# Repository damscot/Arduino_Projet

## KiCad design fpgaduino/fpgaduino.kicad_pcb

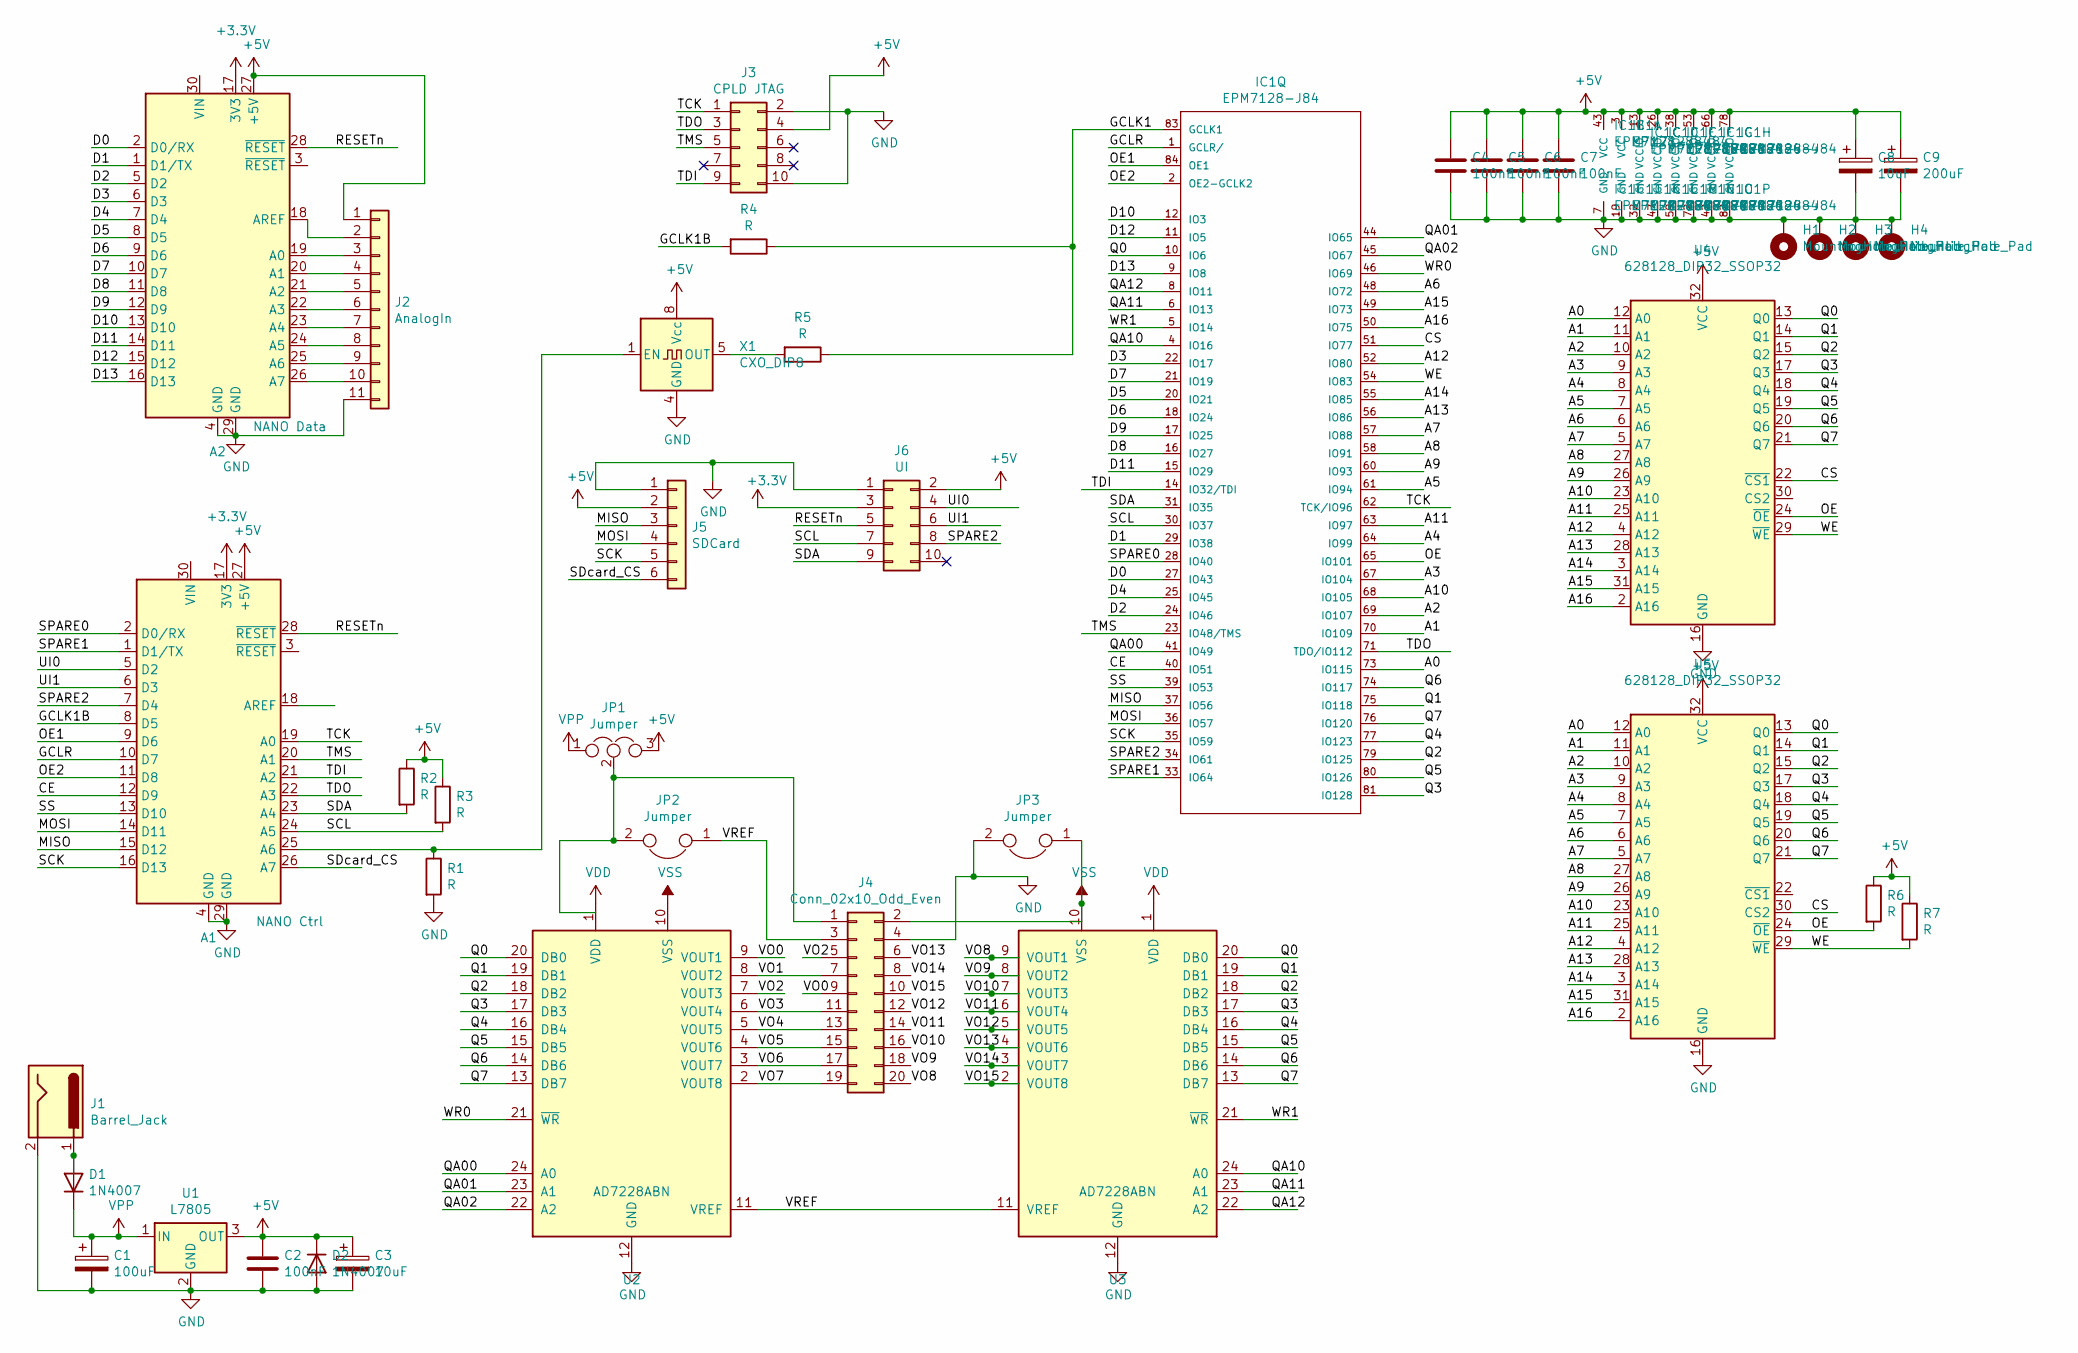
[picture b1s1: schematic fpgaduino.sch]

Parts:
A1: NANO Ctrl; Arduino_Nano
A2: NANO Data; Arduino_Nano
C1: 100uF; C_Radial_D6.3mm_H11.0mm_P2.50mm
C2, C4, C5, C6, C7: 100nF; C_Rect_L7.0mm_W2.0mm_P5.00mm
C3, C8: 10uF; C_Radial_D6.3mm_H11.0mm_P2.50mm
C9: 200uF; C_Radial_D6.3mm_H11.0mm_P2.50mm
D1, D2: 1N4007; D_DO-41_SOD81_P10.16mm_Horizontal
H1, H2, H3, H4: MountingHole_Pad; MountingHole_3.2mm_M3_ISO14580_Pad
IC1: EPM7128-J84; PLCC-84_THT-Socket
J1: Barrel_Jack; BarrelJack_Horizontal
J2: AnalogIn; PinHeader_1x11_P2.54mm_Vertical
J3: CPLD JTAG; IDC-Header_2x05_P2.54mm_Vertical
J4: Conn_02x10_Odd_Even; PinHeader_2x10_P2.54mm_Vertical
J5: SDCard; PinHeader_1x06_P2.54mm_Vertical
J6: UI; IDC-Header_2x05_P2.54mm_Vertical
JP1: Jumper; PinHeader_1x03_P2.54mm_Vertical
JP2, JP3: Jumper; PinHeader_1x02_P2.54mm_Vertical
R1, R2, R3, R4, R5, R6, R7: R; R_Axial_DIN0207_L6.3mm_D2.5mm_P10.16mm_Horizontal
U1: L7805; TO-220-3_Vertical
U2, U3: AD7228ABN; DIP-24_W7.62mm_Socket_LongPads
U4, U5: 628128_DIP32_SSOP32; DIP-32_W15.24mm_Socket_LongPads
X1: CXO_DIP8; Oscillator_DIP-8_LargePads

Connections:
+3V3: A1.17 (3V3), A2.17 (3V3), J6.3
+5V: A1.27 (+5V), A2.27 (+5V), C2.1, C3.1, C4.1, C5.1, C6.1, C7.1, C8.1, C9.1, D2.1 (K), IC1.3 (VCC), IC1.13 (VCCIO), IC1.26 (VCCIO), IC1.38 (VCCIO), IC1.43 (VCC), IC1.53 (VCCIO), IC1.66 (VCCIO), IC1.78 (VCCIO), J2.1, J3.4, J5.2, J6.2, JP1.3, R2.1, R3.1, R6.1, R7.1, U1.3 (OUT), U4.32 (VCC), U5.32 (VCC), X1.8 (Vcc)
/A0: IC1.73 (IO115), U4.12 (A0), U5.12 (A0)
/A1: IC1.70 (IO109), U4.11 (A1), U5.11 (A1)
/A2: IC1.69 (IO107), U4.10 (A2), U5.10 (A2)
/A3: IC1.67 (IO104), U4.9 (A3), U5.9 (A3)
/A4: IC1.64 (IO99), U4.8 (A4), U5.8 (A4)
/A5: IC1.61 (IO94), U4.7 (A5), U5.7 (A5)
/A6: IC1.48 (IO72), U4.6 (A6), U5.6 (A6)
/A7: IC1.57 (IO88), U4.5 (A7), U5.5 (A7)
/A8: IC1.58 (IO91), U4.27 (A8), U5.27 (A8)
/A9: IC1.60 (IO93), U4.26 (A9), U5.26 (A9)
/A10: IC1.68 (IO105), U4.23 (A10), U5.23 (A10)
/A11: IC1.63 (IO97), U4.25 (A11), U5.25 (A11)
/A12: IC1.52 (IO80), U4.4 (A12), U5.4 (A12)
/A13: IC1.56 (IO86), U4.28 (A13), U5.28 (A13)
/A14: IC1.55 (IO85), U4.3 (A14), U5.3 (A14)
/A15: IC1.49 (IO73), U4.31 (A15), U5.31 (A15)
/A16: IC1.50 (IO75), U4.2 (A16), U5.2 (A16)
/CE: A1.12 (D9), IC1.40 (IO51)
/CS: IC1.51 (IO77), U4.22 (~CS1), U5.30 (CS2)
/D0: A2.2 (D0/RX), IC1.27 (IO43)
/D1: A2.1 (D1/TX), IC1.29 (IO38)
/D2: A2.5 (D2), IC1.24 (IO46)
/D3: A2.6 (D3), IC1.22 (IO17)
/D4: A2.7 (D4), IC1.25 (IO45)
/D5: A2.8 (D5), IC1.20 (IO21)
/D6: A2.9 (D6), IC1.18 (IO24)
/D7: A2.10 (D7), IC1.21 (IO19)
/D8: A2.11 (D8), IC1.16 (IO27)
/D9: A2.12 (D9), IC1.17 (IO25)
/D10: A2.13 (D10), IC1.12 (IO3)
/D11: A2.14 (D11), IC1.15 (IO29)
/D12: A2.15 (D12), IC1.11 (IO5)
/D13: A2.16 (D13), IC1.9 (IO8)
/GCLK1: IC1.83 (GCLK1), R4.1, R5.1
/GCLK1B: A1.8 (D5), R4.2
/GCLR: A1.10 (D7), IC1.1 (GCLR/)
/MISO: A1.15 (D12), IC1.37 (IO56), J5.3
/MOSI: A1.14 (D11), IC1.36 (IO57), J5.4
/OE: IC1.65 (IO101), R6.2, U4.24 (~OE), U5.24 (~OE)
/OE1: A1.9 (D6), IC1.84 (OE1)
/OE2: A1.11 (D8), IC1.2 (OE2-GCLK2)
/Q0: IC1.10 (IO6), U2.20 (DB0), U3.20 (DB0), U4.13 (Q0), U5.13 (Q0)
/Q1: IC1.75 (IO118), U2.19 (DB1), U3.19 (DB1), U4.14 (Q1), U5.14 (Q1)
/Q2: IC1.79 (IO125), U2.18 (DB2), U3.18 (DB2), U4.15 (Q2), U5.15 (Q2)
/Q3: IC1.81 (IO128), U2.17 (DB3), U3.17 (DB3), U4.17 (Q3), U5.17 (Q3)
/Q4: IC1.77 (IO123), U2.16 (DB4), U3.16 (DB4), U4.18 (Q4), U5.18 (Q4)
/Q5: IC1.80 (IO126), U2.15 (DB5), U3.15 (DB5), U4.19 (Q5), U5.19 (Q5)
/Q6: IC1.74 (IO117), U2.14 (DB6), U3.14 (DB6), U4.20 (Q6), U5.20 (Q6)
/Q7: IC1.76 (IO120), U2.13 (DB7), U3.13 (DB7), U4.21 (Q7), U5.21 (Q7)
/QA00: IC1.41 (IO49), U2.24 (A0)
/QA01: IC1.44 (IO65), U2.23 (A1)
/QA02: IC1.45 (IO67), U2.22 (A2)
/QA10: IC1.4 (IO16), U3.24 (A0)
/QA11: IC1.6 (IO13), U3.23 (A1)
/QA12: IC1.8 (IO11), U3.22 (A2)
/RESETn: A1.28 (~RESET), A2.28 (~RESET), J6.5
/SCK: A1.16 (D13), IC1.35 (IO59), J5.5
/SCL: A1.24 (A5), IC1.30 (IO37), J6.7, R3.2
/SDA: A1.23 (A4), IC1.31 (IO35), J6.9, R2.2
/SDcard_CS: A1.26 (A7), J5.6
/SPARE0: A1.2 (D0/RX), IC1.28 (IO40)
/SPARE1: A1.1 (D1/TX), IC1.33 (IO64)
/SPARE2: A1.7 (D4), IC1.34 (IO61), J6.8
/SS: A1.13 (D10), IC1.39 (IO53)
/TCK: A1.19 (A0), IC1.62 (TCK/IO96), J3.1
/TDI: A1.21 (A2), IC1.14 (IO32/TDI), J3.9
/TDO: A1.22 (A3), IC1.71 (TDO/IO112), J3.3
/TMS: A1.20 (A1), IC1.23 (IO48/TMS), J3.5
/UI0: A1.5 (D2), J6.4
/UI1: A1.6 (D3), J6.6
/VO0: J4.9, U2.9 (VOUT1)
/VO1: J4.7, U2.8 (VOUT2)
/VO2: J4.5, U2.7 (VOUT3)
/VO3: J4.11, U2.6 (VOUT4)
/VO4: J4.13, U2.5 (VOUT5)
/VO5: J4.15, U2.4 (VOUT6)
/VO6: J4.17, U2.3 (VOUT7)
/VO7: J4.19, U2.2 (VOUT8)
/VO8: J4.20, U3.9 (VOUT1)
/VO9: J4.18, U3.8 (VOUT2)
/VO10: J4.16, U3.7 (VOUT3)
/VO11: J4.14, U3.6 (VOUT4)
/VO12: J4.12, U3.5 (VOUT5)
/VO13: J4.6, U3.4 (VOUT6)
/VO14: J4.8, U3.3 (VOUT7)
/VO15: J4.10, U3.2 (VOUT8)
/VREF: J4.3, JP2.1, U2.11 (VREF), U3.11 (VREF)
/WE: IC1.54 (IO83), R7.2, U4.29 (~WE), U5.29 (~WE)
/WR0: IC1.46 (IO69), U2.21 (~WR)
/WR1: IC1.5 (IO14), U3.21 (~WR)
GND: A1.4 (GND), A1.29 (GND), A2.4 (GND), A2.29 (GND), C1.2, C2.2, C3.2, C4.2, C5.2, C6.2, C7.2, C8.2, C9.2, D2.2 (A), H1.1, H2.1, H3.1, H4.1, IC1.7 (GND), IC1.19 (GND), IC1.32 (GND), IC1.42 (GND), IC1.47 (GND), IC1.59 (GND), IC1.72 (GND), IC1.82 (GND), J1.2, J2.11, J3.2, J3.10, J4.4, J5.1, J6.1, JP3.2, R1.2, U1.2 (GND), U2.12 (GND), U3.12 (GND), U4.16 (GND), U5.16 (GND), X1.4 (GND)
unnamed: A1.25 (A6), R1.1, X1.1 (EN)
unnamed: A2.18 (AREF), J2.2
unnamed: A2.19 (A0), J2.3
unnamed: A2.20 (A1), J2.4
unnamed: A2.21 (A2), J2.5
unnamed: A2.22 (A3), J2.6
unnamed: A2.23 (A4), J2.7
unnamed: A2.24 (A5), J2.8
unnamed: A2.25 (A6), J2.9
unnamed: A2.26 (A7), J2.10
unnamed: D1.2 (A), J1.1
unnamed: J4.1, JP1.2, JP2.2
unnamed: R5.2, X1.5 (OUT)
VDD: U2.1 (VDD), U3.1 (VDD)
VPP: C1.1, D1.1 (K), JP1.1, U1.1 (IN)
VSS: J4.2, JP3.1, U2.10 (VSS), U3.10 (VSS)

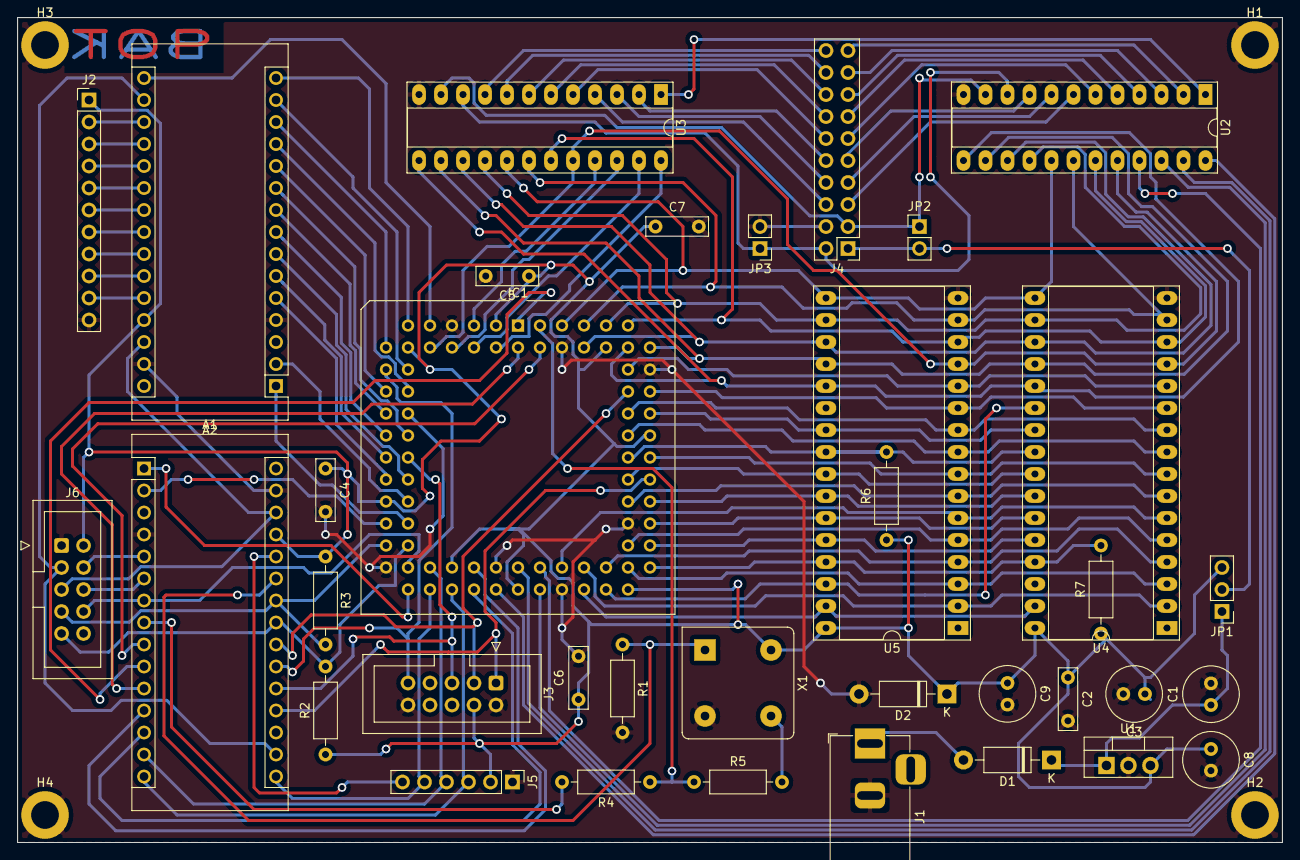
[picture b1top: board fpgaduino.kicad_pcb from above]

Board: 2 copper layers, 146.1 x 95.2 mm, 40 parts (0 on the bottom side), 109 nets.

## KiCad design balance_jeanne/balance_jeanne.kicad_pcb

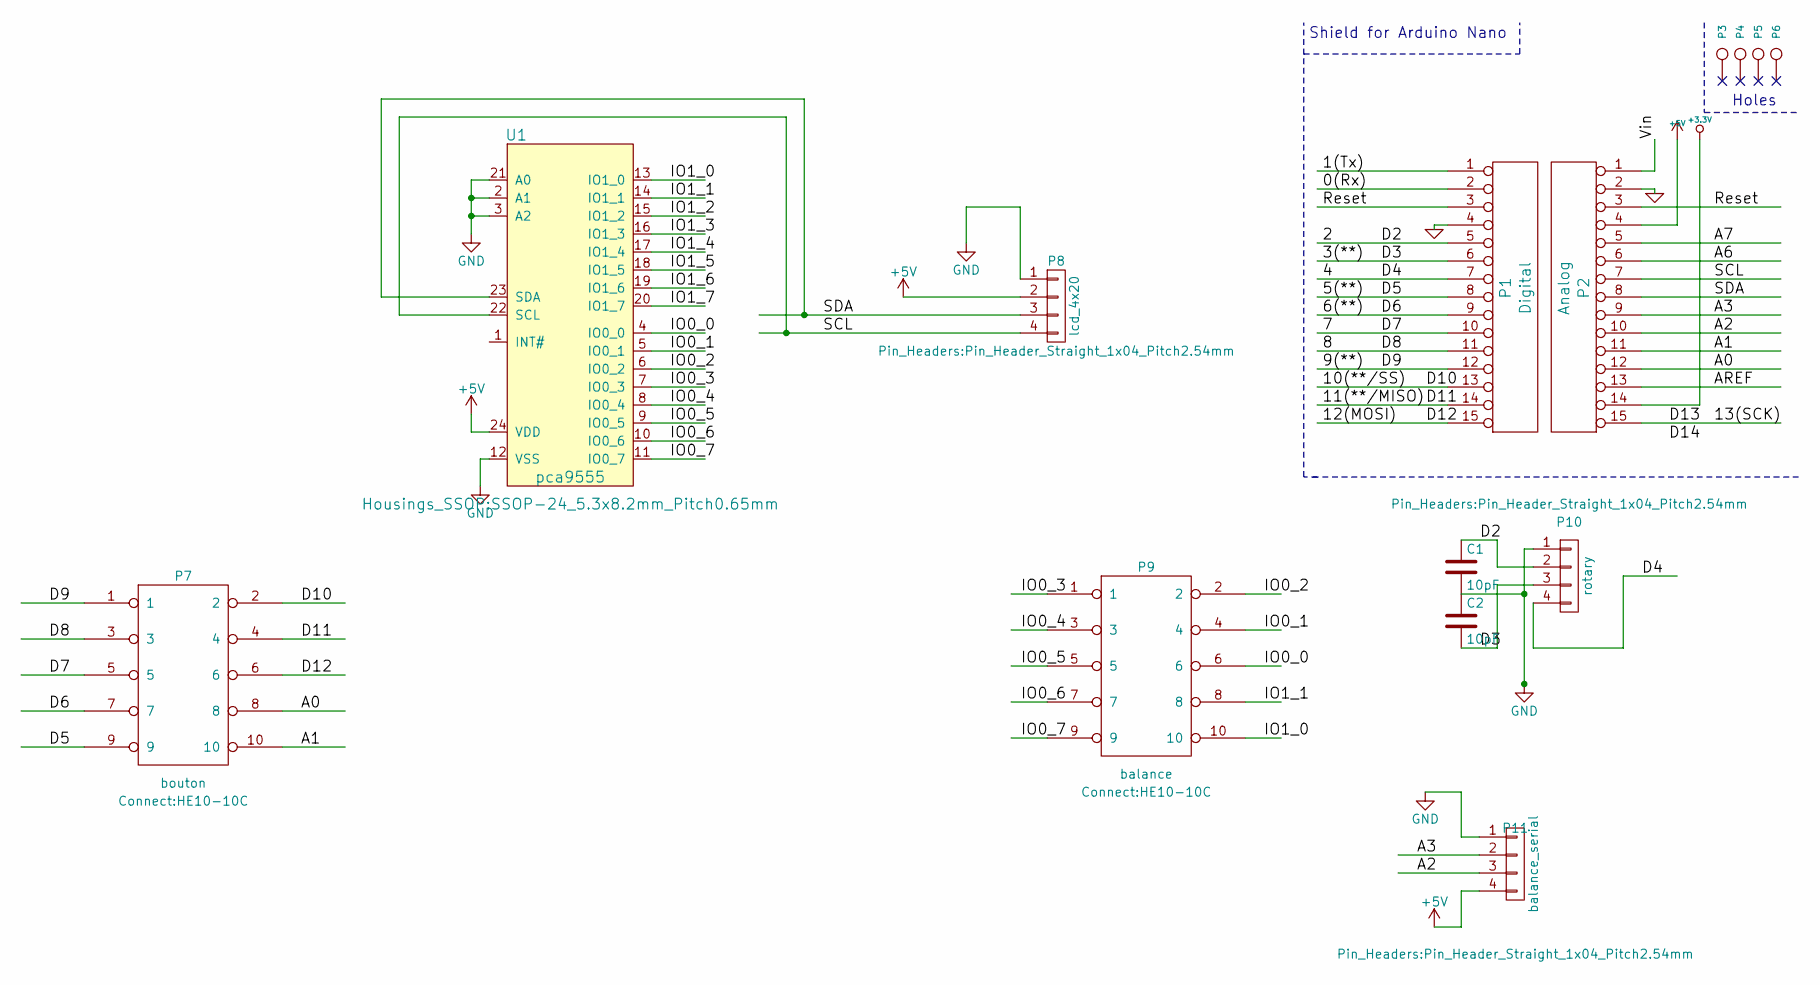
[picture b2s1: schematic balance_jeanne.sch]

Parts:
C1, C2: 10pF; Pin_Header_Straight_1x02_Pitch2.54mm
P1: Digital; Socket_Strip_Arduino_1x15
P2: Analog; Socket_Strip_Arduino_1x15
P3, P4, P5, P6: CONN_1; 1pin_Nano
P7: bouton; HE10-10C
P8: lcd_4x20; Pin_Header_Straight_1x04_Pitch2.54mm
P9: balance; HE10-10C
P10: rotary; Pin_Header_Straight_1x04_Pitch2.54mm
P11: balance_serial; Pin_Header_Straight_1x04_Pitch2.54mm
U1: pca9555; SSOP-24_5.3x8.2mm_Pitch0.65mm

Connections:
+3.3V: P2.14
+5V: P2.4, P8.2, P11.4, U1.24 (VDD)
/0(Rx): P1.2
/1(Tx): P1.1
/2: C1.1, P1.5, P10.2
/3(**): C2.2, P1.6, P10.3
/4: P1.7, P10.4
/5(**): P1.8, P7.9
/6(**): P1.9, P7.7
/7: P1.10, P7.5
/8: P1.11, P7.3
/9(**): P1.12, P7.1
/10(**/SS): P1.13, P7.2
/11(**/MISO): P1.14, P7.4
/12(MOSI): P1.15 (p15), P7.6
/13(SCK): P2.15 (p15)
/A0: P2.12, P7.8
/A1: P2.11, P7.10
/A2: P2.10, P11.3
/A3: P2.9, P11.2
/A6: P2.6
/A7: P2.5
/AREF: P2.13
/IO0_0: P9.6, U1.4 (IO0_0)
/IO0_1: P9.4, U1.5 (IO0_1)
/IO0_2: P9.2, U1.6 (IO0_2)
/IO0_3: P9.1, U1.7 (IO0_3)
/IO0_4: P9.3, U1.8 (IO0_4)
/IO0_5: P9.5, U1.9 (IO0_5)
/IO0_6: P9.7, U1.10 (IO0_6)
/IO0_7: P9.9, U1.11 (IO0_7)
/IO1_0: P9.10, U1.13 (IO1_0)
/IO1_1: P9.8, U1.14 (IO1_1)
/IO1_2: U1.15 (IO1_2)
/IO1_3: U1.16 (IO1_3)
/IO1_4: U1.17 (IO1_4)
/IO1_5: U1.18 (IO1_5)
/IO1_6: U1.19 (IO1_6)
/IO1_7: U1.20 (IO1_7)
/Reset: P1.3, P2.3
/SCL: P2.7, P8.4, U1.22 (SCL)
/SDA: P2.8, P8.3, U1.23 (SDA)
/Vin: P2.1
GND: C1.2, C2.1, P1.4, P2.2, P8.1, P10.1, P11.1, U1.2 (A1), U1.3 (A2), U1.12 (VSS), U1.21 (A0)

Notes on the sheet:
Holes
Shield for Arduino Nano

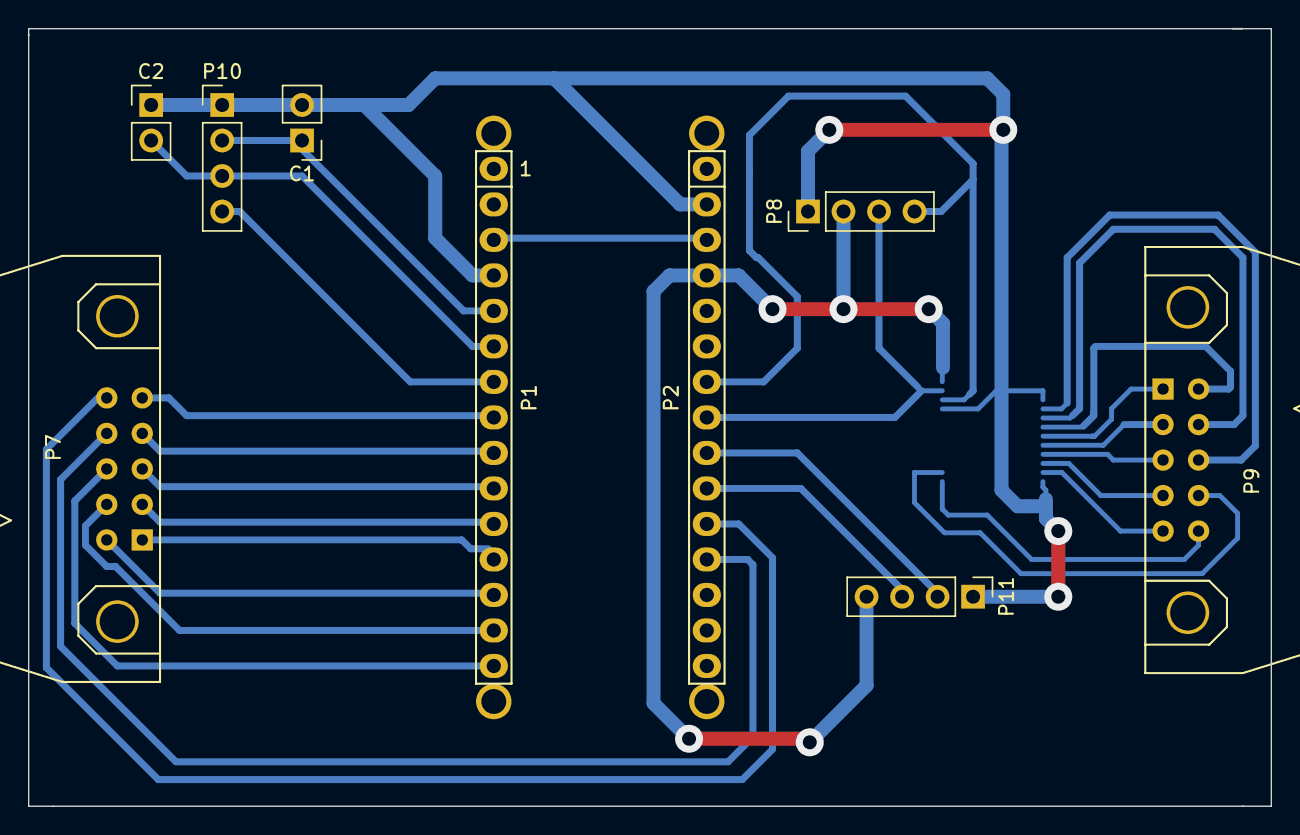
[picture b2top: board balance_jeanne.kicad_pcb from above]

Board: 2 copper layers, 88.9 x 55.6 mm, 14 parts (1 on the bottom side), 30 nets.

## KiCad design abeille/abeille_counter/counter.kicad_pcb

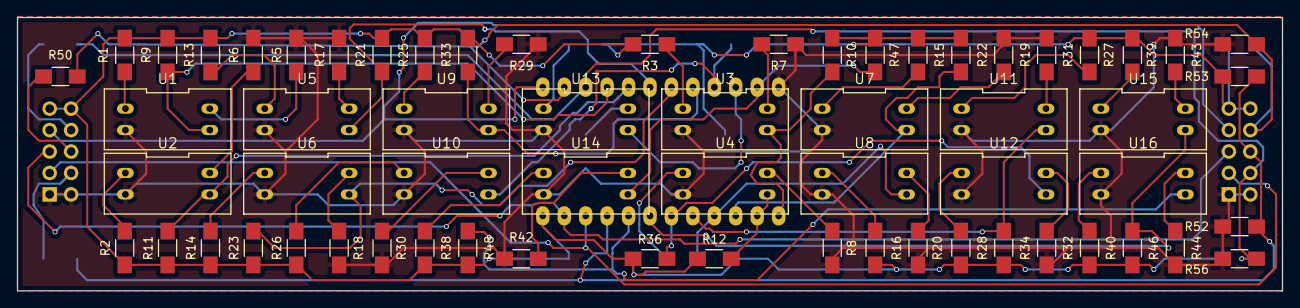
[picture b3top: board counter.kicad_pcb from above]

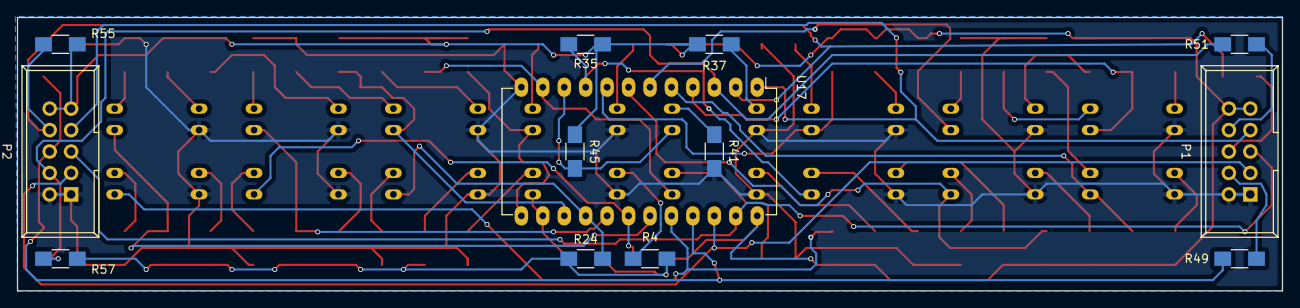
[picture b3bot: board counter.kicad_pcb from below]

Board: 2 copper layers, 149.9 x 32.4 mm, 76 parts (13 on the bottom side), 59 nets.

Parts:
P1, P2: HE10-10; IDC_Header_Straight_10pins
R1, R2, R3, R4, R5, R6, R7, R8, R13, R14, R15, R16, R17, R18, R19, R20, R25, R26, R27, R28, R29, R30, R31, R32, R37, R38, R39, R40, R41, R42, R43, R44: 1K; R_1206_HandSoldering
R9, R10, R11, R12, R21, R22, R23, R24, R33, R34, R35, R36, R45, R46, R47, R48: 100K; R_1206_HandSoldering
R49, R50, R51, R52, R53, R54, R55, R56, R57: 0; R_1206_HandSoldering
U1: IN_0; ITR9608_DIP-4_0_ELL
U2: OUT_0; ITR9608_DIP-4_0_ELL
U3: IN_4; ITR9608_DIP-4_0_ELL
U4: OUT_4; ITR9608_DIP-4_0_ELL
U5: IN_1; ITR9608_DIP-4_0_ELL
U6: OUT_1; ITR9608_DIP-4_0_ELL
U7: IN_5; ITR9608_DIP-4_0_ELL
U8: OUT_5; ITR9608_DIP-4_0_ELL
U9: IN_2; ITR9608_DIP-4_0_ELL
U10: OUT_2; ITR9608_DIP-4_0_ELL
U11: IN_6; ITR9608_DIP-4_0_ELL
U12: OUT_6; ITR9608_DIP-4_0_ELL
U13: IN_3; ITR9608_DIP-4_0_ELL
U14: OUT_3; ITR9608_DIP-4_0_ELL
U15: IN_7; ITR9608_DIP-4_0_ELL
U16: OUT_7; ITR9608_DIP-4_0_ELL
U17: pca9555; DIP-24_W15.24mm_LongPads

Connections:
+5V: P1.9, P1.10, P2.9, P2.10, R1.1, R2.1, R3.1, R4.1, R9.1, R10.1, R11.1, R12.1, R13.1, R14.1, R15.1, R16.1, R21.1, R22.1, R23.1, R24.1, R25.1, R26.1, R27.1, R28.1, R33.1, R34.1, R35.1, R36.1, R37.1, R38.1, R39.1, R40.1, R45.1, R46.1, R47.1, R48.1, R53.2, R55.2, R57.2, U17.24
/A0: P2.6, R49.1, R52.2, R53.1, U17.21
/A1: P2.8, R50.1, R54.2, R55.1, U17.2
/A2: P2.4, R51.1, R56.2, R57.1, U17.3
/D0: R9.2, U1.3, U17.4
/D1: R11.2, U2.3, U17.5
/D2: R21.2, U5.3, U17.6
/D3: R23.2, U6.3, U17.7
/D4: R33.2, U9.3, U17.8
/D5: R35.2, U10.3, U17.9
/D6: R45.2, U13.3, U17.10
/D7: R47.2, U14.3, U17.11
/D8: R10.2, U3.3, U17.13
/D9: R12.2, U4.3, U17.14
/D10: R22.2, U7.3, U17.15
/D11: R24.2, U8.3, U17.16
/D12: R34.2, U11.3, U17.17
/D13: R36.2, U12.3, U17.18
/D14: R46.2, U15.3, U17.19
/D15: R48.2, U16.3, U17.20
/INT#: P1.7, P2.7, U17.1
/SCL: P1.3, P2.3, U17.22
/SDA: P1.5, P2.5, U17.23
GND: P1.1, P1.2, P2.1, P2.2, R5.2, R6.2, R7.2, R8.2, R17.2, R18.2, R19.2, R20.2, R29.2, R30.2, R31.2, R32.2, R41.2, R42.2, R43.2, R44.2, R52.1, R54.1, R56.1, U1.2, U2.2, U3.2, U4.2, U5.2, U6.2, U7.2, U8.2, U9.2, U10.2, U11.2, U12.2, U13.2, U14.2, U15.2, U16.2, U17.12
unnamed: P1.4, R49.2
unnamed: P1.6, R50.2
unnamed: P1.8, R51.2
unnamed: R1.2, U1.1
unnamed: R2.2, U2.1
unnamed: R3.2, U3.1
unnamed: R4.2, U4.1
unnamed: R5.1, U1.4
unnamed: R6.1, U2.4
unnamed: R7.1, U3.4
unnamed: R8.1, U4.4
unnamed: R13.2, U5.1
unnamed: R14.2, U6.1
unnamed: R15.2, U7.1
unnamed: R16.2, U8.1
unnamed: R17.1, U5.4
unnamed: R18.1, U6.4
unnamed: R19.1, U7.4
unnamed: R20.1, U8.4
unnamed: R25.2, U9.1
unnamed: R26.2, U10.1
unnamed: R27.2, U11.1
unnamed: R28.2, U12.1
unnamed: R29.1, U9.4
unnamed: R30.1, U10.4
unnamed: R31.1, U11.4
unnamed: R32.1, U12.4
unnamed: R37.2, U13.1
unnamed: R38.2, U14.1
unnamed: R39.2, U15.1
unnamed: R40.2, U16.1
unnamed: R41.1, U13.4
unnamed: R42.1, U14.4
unnamed: R43.1, U15.4
unnamed: R44.1, U16.4

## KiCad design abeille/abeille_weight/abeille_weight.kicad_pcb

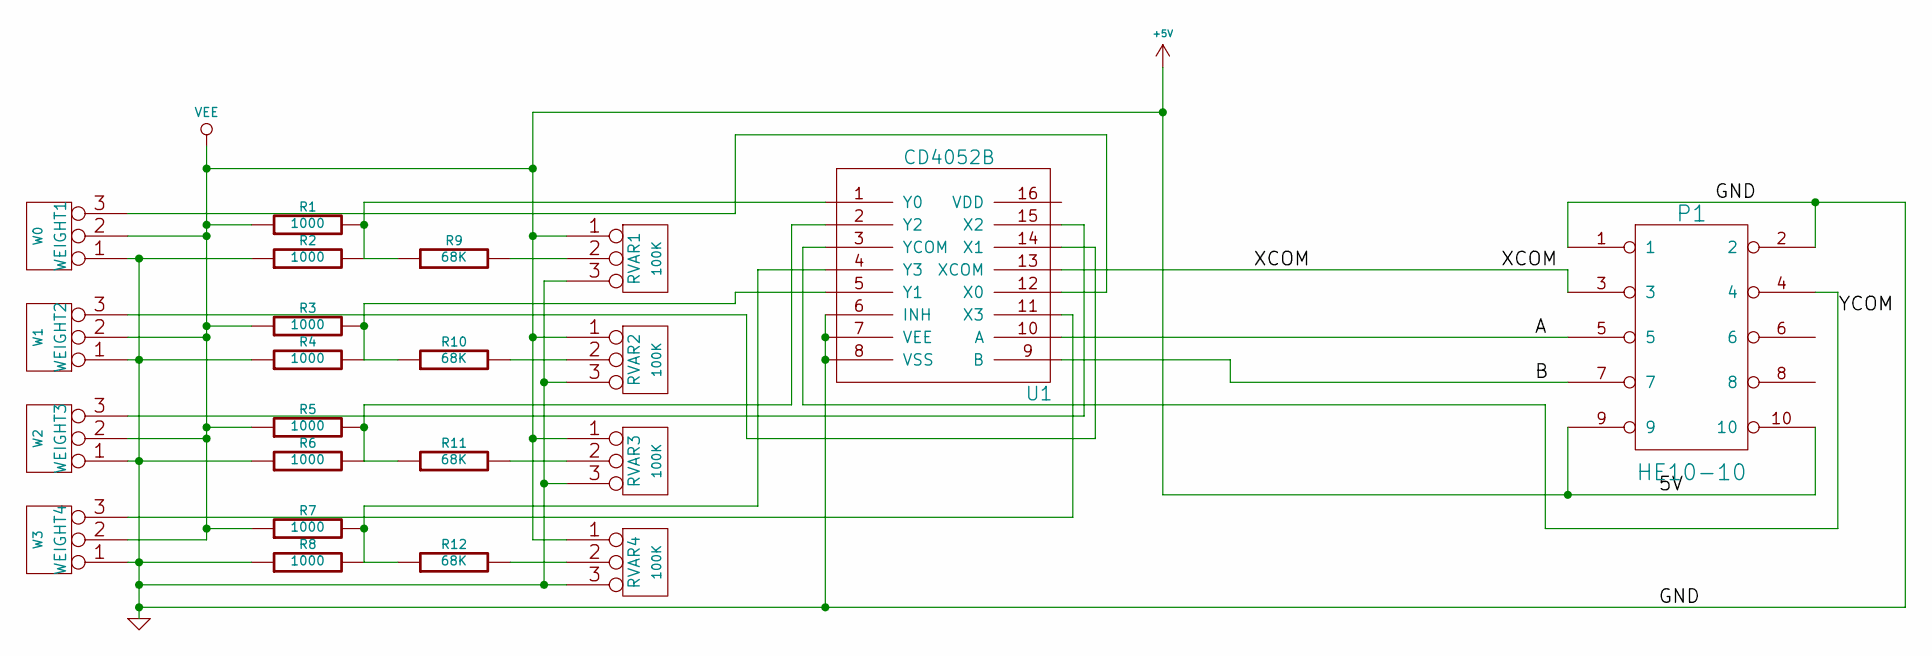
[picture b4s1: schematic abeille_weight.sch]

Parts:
P1: HE10-10
R1, R2, R3, R4, R5, R6, R7, R8: 1000
R9, R10, R11, R12: 68K
RVAR1, RVAR2, RVAR3, RVAR4: 100K
U1: CD4052B
WEIGHT1: W0
WEIGHT2: W1
WEIGHT3: W2
WEIGHT4: W3

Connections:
+5V: P1.9, P1.10, R1.1, R3.1, R5.1, R7.1, RVAR1.1, RVAR2.1, RVAR3.1, RVAR4.1, U1.16 (VDD), WEIGHT1.2 (PM), WEIGHT2.2 (PM), WEIGHT3.2 (PM), WEIGHT4.2 (PM); also elsewhere on the board
/A: P1.5, U1.10 (A)
/B: P1.7, U1.9 (B)
/DT: P1.8; also elsewhere on the board
/SCK: P1.6; also elsewhere on the board
/XCOM: P1.3, U1.13 (XCOM); also elsewhere on the board
/YCOM: P1.4, U1.3 (YCOM); also elsewhere on the board
GND: P1.1, P1.2, R2.1, R4.1, R6.1, R8.1, RVAR1.3, RVAR2.3, RVAR3.3, RVAR4.3, U1.6 (INH), U1.7 (VEE), U1.8 (VSS), WEIGHT1.1, WEIGHT2.1, WEIGHT3.1, WEIGHT4.1; also elsewhere on the board
unnamed: R1.2, R2.2, R9.1, U1.1 (Y0)
unnamed: R9.2, RVAR1.2 (PM)
unnamed: R3.2, R4.2, R10.1, U1.5 (Y1)
unnamed: R10.2, RVAR2.2 (PM)
unnamed: R5.2, R6.2, R11.1, U1.2 (Y2)
unnamed: R11.2, RVAR3.2 (PM)
unnamed: R7.2, R8.2, R12.1, U1.4 (Y3)
unnamed: R12.2, RVAR4.2 (PM)
unnamed: U1.11 (X3), WEIGHT4.3
unnamed: U1.12 (X0), WEIGHT1.3
unnamed: U1.14 (X1), WEIGHT2.3
unnamed: U1.15 (X2), WEIGHT3.3

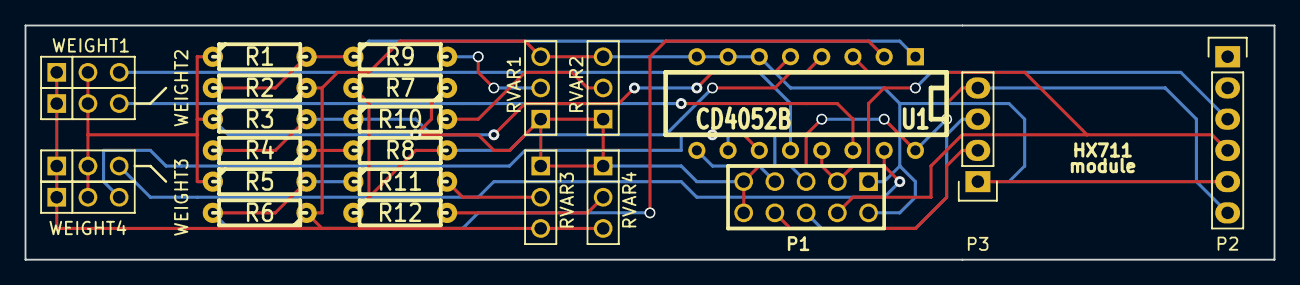
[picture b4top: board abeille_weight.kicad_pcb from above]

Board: 2 copper layers, 101.6 x 19.0 mm, 24 parts (0 on the bottom side), 20 nets.

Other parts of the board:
P2: CONN_01X06; Pin_Header_Straight_1x06
P3: CONN_01X04; Pin_Header_Straight_1x04

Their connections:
+5V: P2.6, P3.4; also elsewhere on the board
/DT: P3.2; also elsewhere on the board
/SCK: P3.3; also elsewhere on the board
/XCOM: P2.3; also elsewhere on the board
/YCOM: P2.4; also elsewhere on the board
GND: P2.5, P3.1; also elsewhere on the board

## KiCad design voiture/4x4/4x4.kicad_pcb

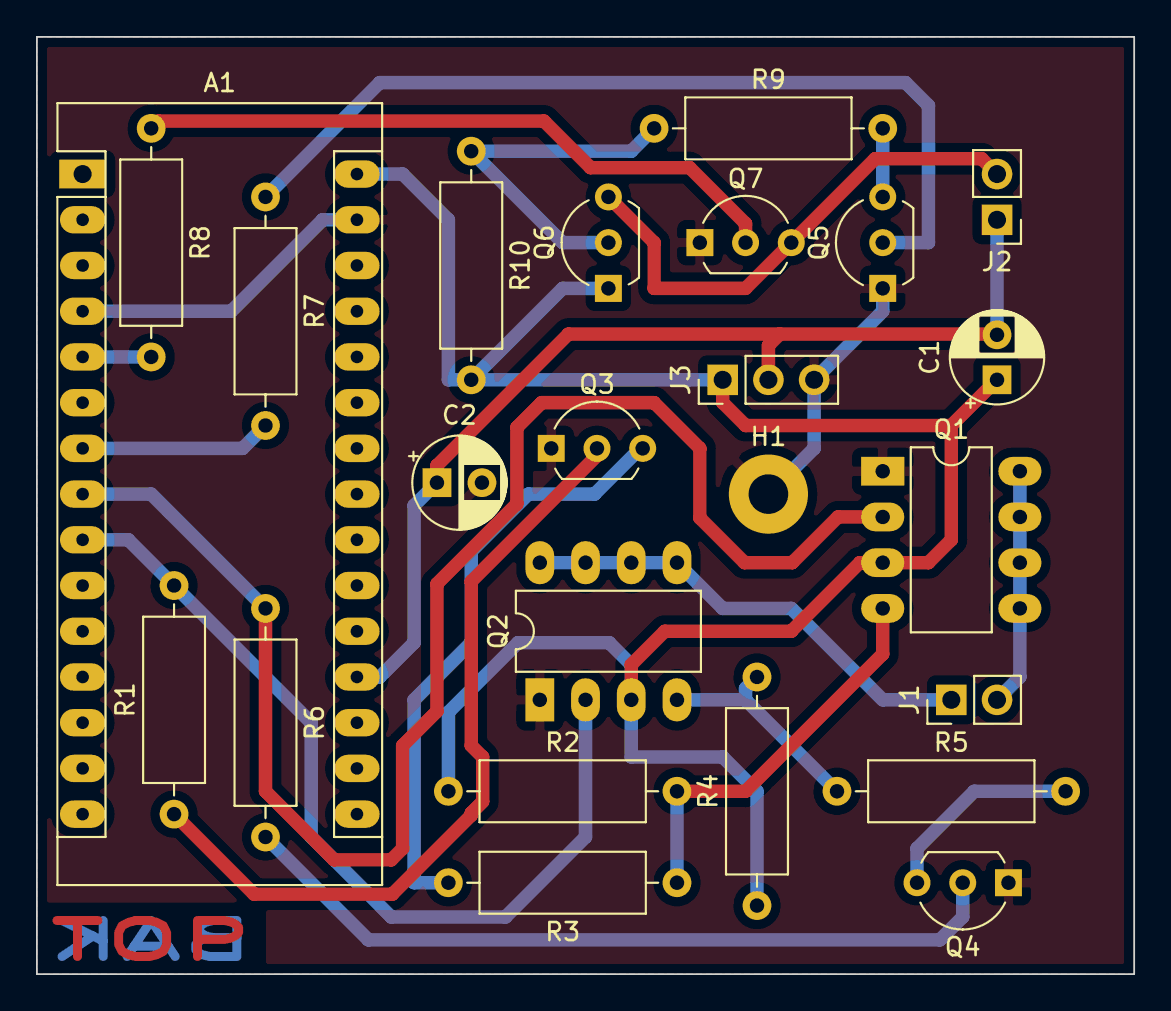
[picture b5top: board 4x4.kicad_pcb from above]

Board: 2 copper layers, 61.0 x 52.1 mm, 24 parts (0 on the bottom side), 20 nets.

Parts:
A1: Arduino_Nano_v3.x; Arduino_Nano
C1, C2: 220uF; CP_Radial_D5.0mm_P2.50mm
H1: MountingHole_Pad; MountingHole_2.2mm_M2_Pad
J1: main motor terminal; PinHeader_1x02_P2.54mm_Vertical
J2: direction terminal; PinHeader_1x02_P2.54mm_Vertical
J3: power input; PinHeader_1x03_P2.54mm_Vertical
Q1, Q2: AOP605; DIP-8_W7.62mm_LongPads
Q3, Q4, Q5: S0918; TO-92L_Inline_Wide
Q6: S0915; TO-92L_Inline_Wide
Q7: S0913; TO-92L_Inline_Wide
R1, R6: 22K; R_Axial_DIN0309_L9.0mm_D3.2mm_P12.70mm_Horizontal
R2, R4, R10: 10K; R_Axial_DIN0309_L9.0mm_D3.2mm_P12.70mm_Horizontal
R3, R5: 100; R_Axial_DIN0309_L9.0mm_D3.2mm_P12.70mm_Horizontal
R7, R8, R9: 470; R_Axial_DIN0309_L9.0mm_D3.2mm_P12.70mm_Horizontal

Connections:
/FWD: A1.8, Q1.2, R6.1
/LEFT: A1.7, R7.2
/REV: A1.9, Q2.2, R1.2
/RIGHT: A1.5, R8.2
GND: A1.4, A1.29, C2.2, H1.1, J3.3, Q1.1, Q2.1, Q3.1, Q4.1, Q5.1, Q7.1
unnamed: J1.1, Q2.5, Q2.6, Q2.7, Q2.8
unnamed: J1.2, Q1.5, Q1.6, Q1.7, Q1.8
unnamed: J2.2, Q6.3, Q7.3
unnamed: Q1.4, R2.2, R3.1
unnamed: Q2.4, R4.2, R5.1
unnamed: Q3.2, R1.1
unnamed: Q3.3, R3.2
unnamed: Q4.2, R6.2
unnamed: Q4.3, R5.2
unnamed: Q5.2, R7.1
unnamed: Q5.3, R9.2
unnamed: Q6.2, R9.1, R10.1
unnamed: Q7.2, R8.1
VCC: A1.30, C1.1, J3.1, Q1.3, Q2.3, Q6.1, R2.1, R4.1, R10.2
VCCQ: A1.19, C1.2, C2.1, J2.1, J3.2

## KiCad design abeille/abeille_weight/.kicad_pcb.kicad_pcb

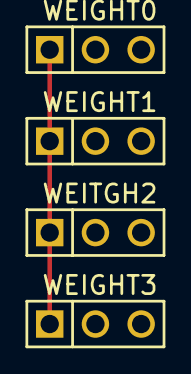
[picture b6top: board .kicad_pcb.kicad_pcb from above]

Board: 2 copper layers, 4 parts (0 on the bottom side), 2 nets.

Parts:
WEIGHT0, WEIGHT1, WEIGHT3: CONN_3; PIN_ARRAY_3X1
WEITGH2: CONN_3; PIN_ARRAY_3X1

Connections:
GND: WEIGHT0.1, WEIGHT1.1, WEIGHT3.1, WEITGH2.1
VEE: WEIGHT0.2, WEIGHT1.2, WEIGHT3.2, WEITGH2.2

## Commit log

2015-12-13 add abeille
2015-12-13 [Benj] add red led
2016-01-03 add some files
2016-01-03 update abeille weight project
2016-02-22 minor modif
2016-02-22 add i2c_detect and lcd_rotary_sw
2016-02-23 abeille counter schematics update
2016-02-23 start placing counter components
2016-02-26 HX711Serial add support for the 4 sensors
2016-02-27 start placing of resistor of abeille_counter
2016-06-02 first final routing version of abeille counter
2016-12-24 pousse comme un sale tous les petits projet... backup
2017-01-16 add balance project
2017-02-25 premiere mouture de la balance augmente
2017-02-26 touche clavier fonctionnelles
2017-11-09 ajout de quelques articles dans la balance
2017-11-10 ploting several temp sensor with serialplot
2019-09-16 nouveau boitier IR_Thermo
    boitier pla impression 3D IR Thermo
2019-09-16 Voiture Telecommande nouvelle version
    Mode 2.4GHz et nouveau chassis nikko.
2019-09-16 Initial Temp Control
    Premiere version
    merge rapide menusystem LCD Rotary SW et DS18B20
2019-09-18 update balance jeanne
    Aucune idée des modifs en cours... :-P
2020-06-23 ajout support double voiture
2020-06-29 voiture_4x4
2020-06-30 fpgaduino
    CPLD 7128 altera + 2 Arduino + 2 x8 channel DAC + 2 Sample SRAMs
2020-07-30 Pompe évacuation dégivrage banque froide Chez Jeanne
    controle d'une pompe en 12V basé arduino.
    schéma classique NPN sur PWM puis PNP puissance pour le moteur (Pin 5).
    Détection du niveau full par floteur sur pin 2.
    Design State Machine + ISR.
